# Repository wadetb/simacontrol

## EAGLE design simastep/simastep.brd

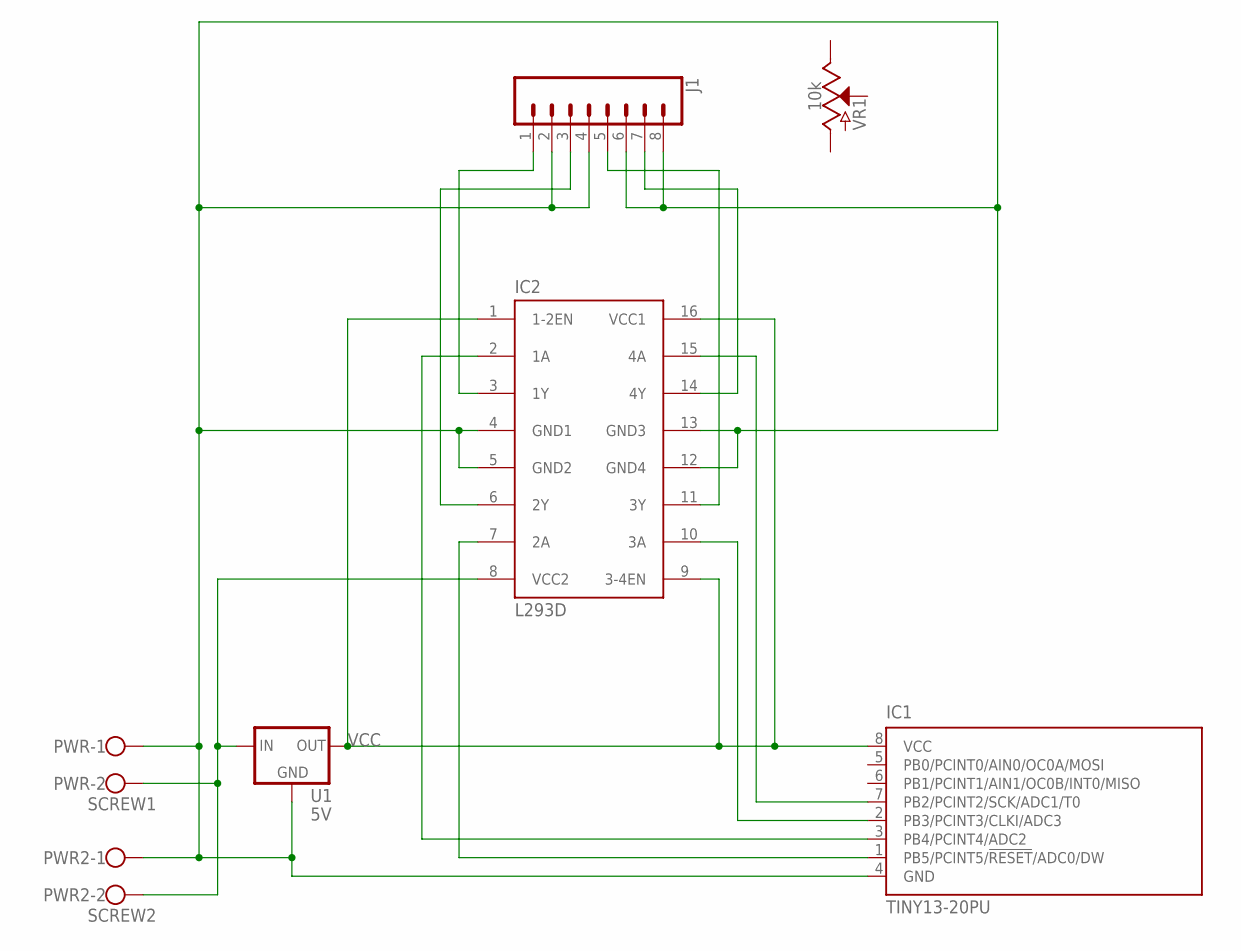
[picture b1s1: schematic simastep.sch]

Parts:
IC1: TINY13-20PU; DIL08
IC2: L293D; DIL16
J1: CONN_083.5MM-8; SCREWTERMINAL-3.5MM-8
PWR: SCREW1; W237-102
PWR2: SCREW2; W237-102
U1: 5V; TO220-IGO
VR1: 10k; POT-PTH-ALPS

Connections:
GND: IC1.4 (GND), IC2.4 (GND1), IC2.5 (GND2), IC2.12 (GND4), IC2.13 (GND3), J1.2, J1.4, J1.6, J1.8, PWR.1, PWR2.1, U1.GND
unnamed: IC2.3 (1Y), J1.1
unnamed: IC2.6 (2Y), J1.3
unnamed: IC2.11 (3Y), J1.5
unnamed: IC2.14 (4Y), J1.7
unnamed: IC1.7 (PB2/PCINT2/SCK/ADC1/T0), IC2.15 (4A)
unnamed: IC1.2 (PB3/PCINT3/CLKI/ADC3), IC2.10 (3A)
unnamed: IC1.3 (PB4/PCINT4/ADC2), IC2.2 (1A)
unnamed: IC1.1 (PB5/PCINT5/!RESET!/ADC0/DW), IC2.7 (2A)
VCC: IC1.8 (VCC), IC2.1 (1-2EN), IC2.9 (3-4EN), IC2.16 (VCC1), U1.OUT
VIN: IC2.8 (VCC2), PWR.2, PWR2.2, U1.IN

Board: 2 copper layers, 7 parts (0 on the bottom side), 11 nets, no tracks yet.

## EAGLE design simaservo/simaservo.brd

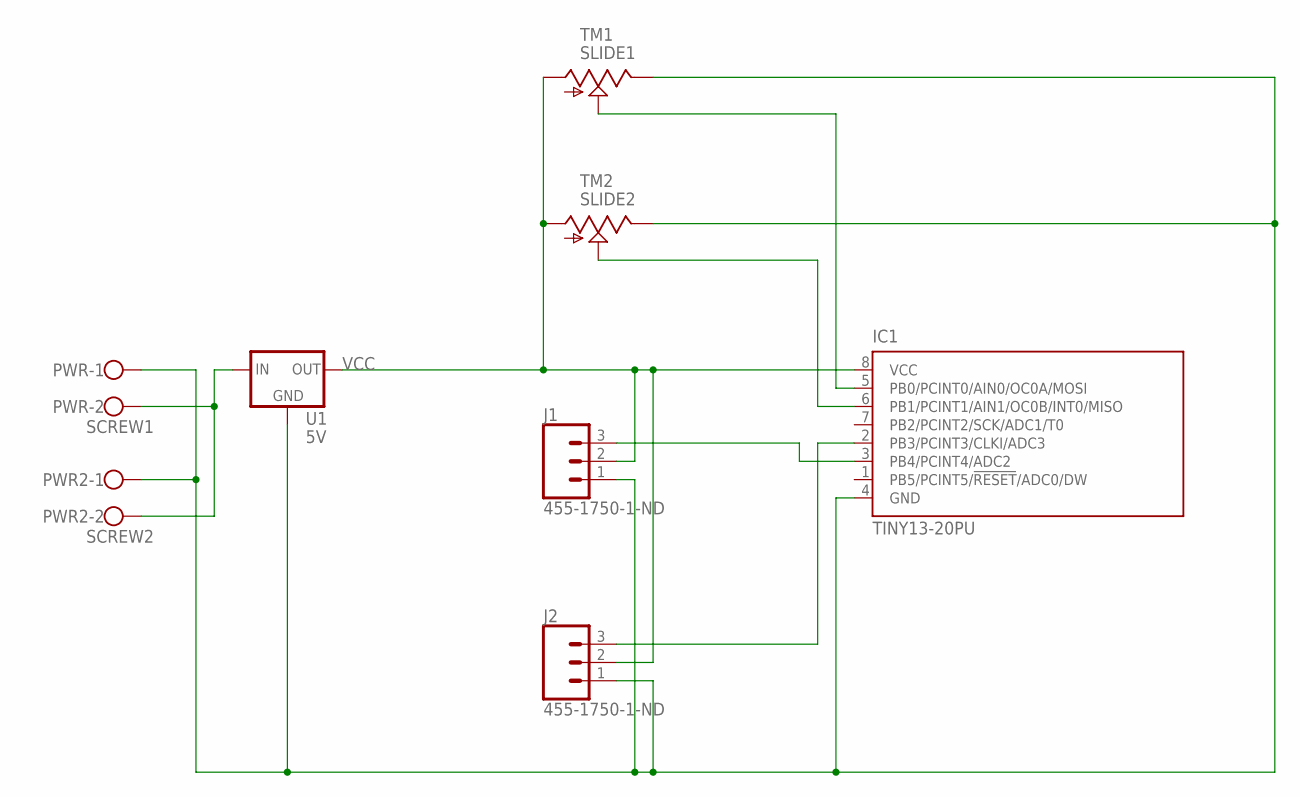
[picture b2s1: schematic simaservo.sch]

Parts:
IC1: TINY13-20PU; DIL08
J1, J2: 455-1750-1-ND; 1X03
PWR: SCREW1; W237-102
PWR2: SCREW2; W237-102
TM1: SLIDE1; SLIDEPOT-60
TM2: SLIDE2; SLIDEPOT-60
U1: 5V; TO220-IGO

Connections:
AIN0: IC1.5 (PB0/PCINT0/AIN0/OC0A/MOSI), TM1.WIPER
GND: IC1.4 (GND), J1.1, J2.1, PWR.1, PWR2.1, TM1.B, TM2.B, U1.GND
unnamed: IC1.6 (PB1/PCINT1/AIN1/OC0B/INT0/MISO), TM2.WIPER
unnamed: IC1.3 (PB4/PCINT4/ADC2), J1.3
unnamed: IC1.2 (PB3/PCINT3/CLKI/ADC3), J2.3
VCC: IC1.8 (VCC), J1.2, J2.2, TM1.A, TM2.A, U1.OUT
VIN: PWR.2, PWR2.2, U1.IN

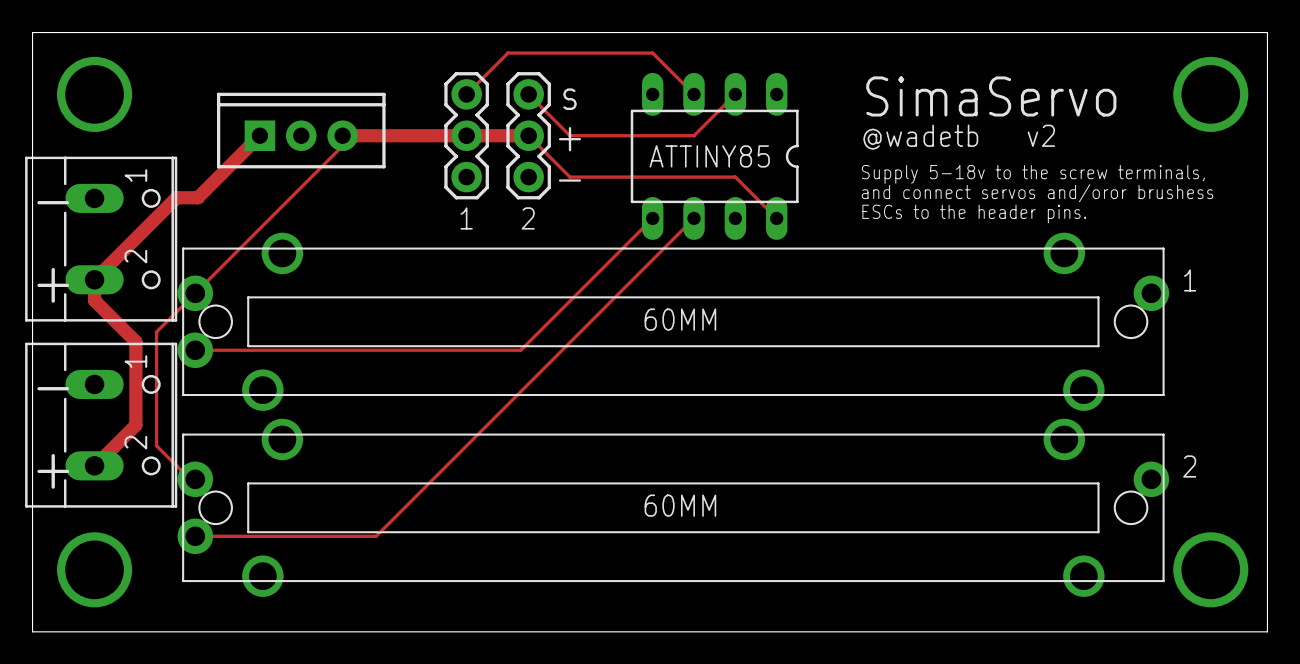
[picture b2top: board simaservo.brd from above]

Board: 2 copper layers, 75.9 x 36.8 mm, 8 parts (0 on the bottom side), 7 nets.

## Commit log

2019-12-27 add simaservo
2019-12-27 add board
2019-12-27 add wip step
2019-12-27 remove pro

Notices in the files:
parts and their libraries:
SparkFun-IC-Power: Licensing: Creative Commons ShareAlike 4.0 International - https://creativecommons.org/licenses/by-sa/4.0
